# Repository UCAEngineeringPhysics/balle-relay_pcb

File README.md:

# balle-relay_pcb
PCB design for relaying balle's signals

## Schematic

## PCB0121

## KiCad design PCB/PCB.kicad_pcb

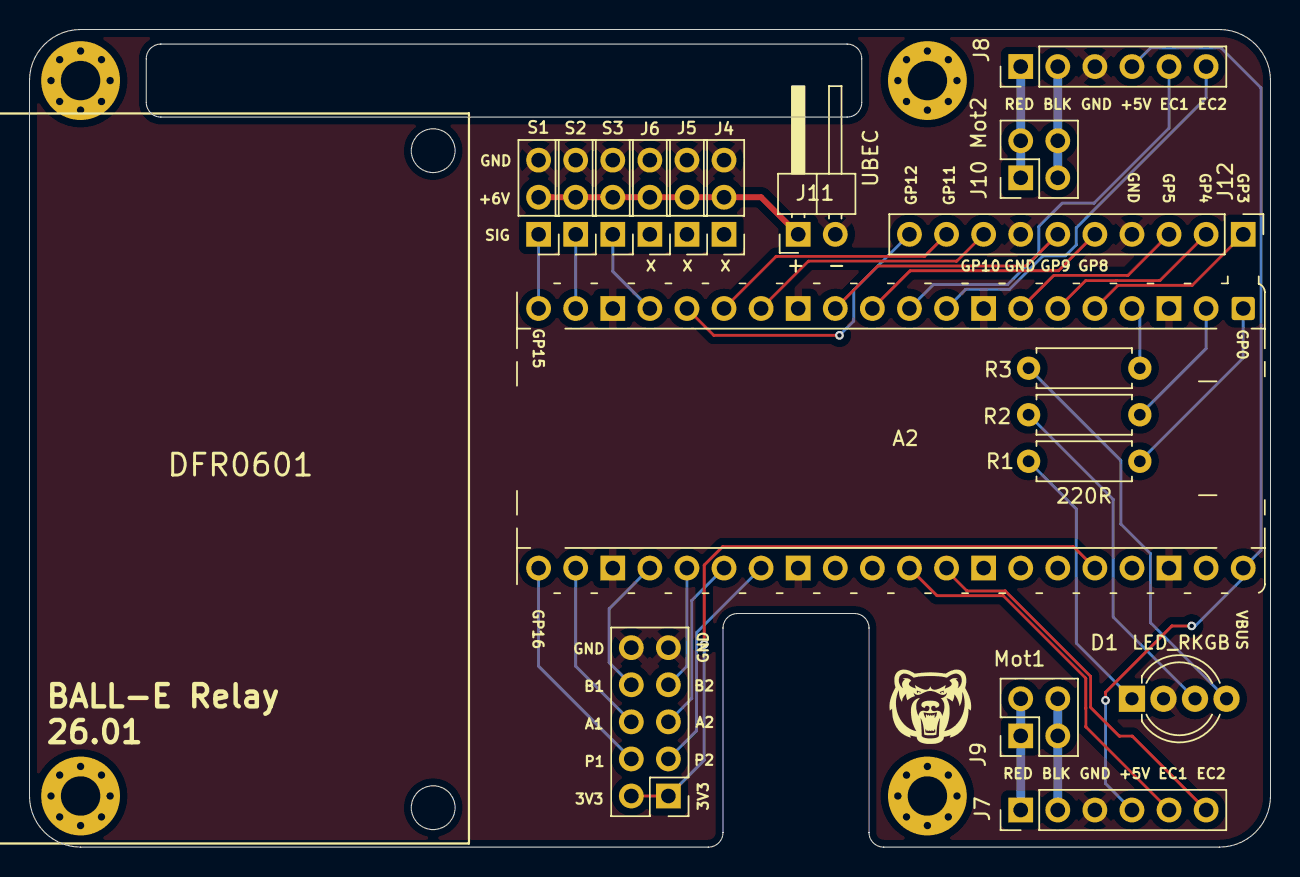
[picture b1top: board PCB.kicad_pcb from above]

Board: 4 copper layers, 85.0 x 56.0 mm, 22 parts (0 on the bottom side), 35 nets.

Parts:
A2: RaspberryPi_Pico; RaspberryPi_Pico_THT
D1: LED_RKGB; LED_D5.0mm-4_RGB_Wide_Pins
H1, H2, H3, H4: MountingHole_Pad; MountingHole_2.7mm_M2.5_Pad_Via
J4: Servo_Conn_4; PinHeader_1x03_P2.54mm_Vertical
J5: Servo_Conn_5; PinHeader_1x03_P2.54mm_Vertical
J6: Servo_Conn_6; PinHeader_1x03_P2.54mm_Vertical
J7: Mot1_Conn; PinHeader_1x06_P2.54mm_Vertical
J8: Mot2_Conn; PinHeader_1x06_P2.54mm_Vertical
J9: Mot1; PinHeader_2x02_P2.54mm_Vertical
J10: Mot2; PinHeader_2x02_P2.54mm_Vertical
J11: UBEC; PinHeader_1x02_P2.54mm_Horizontal
J12: Spare_GPIO_Conn; PinHeader_1x10_P2.54mm_Vertical
MOT_DRV_Conn1: Conn_02x05_Odd_Even; PinHeader_2x05_P2.54mm_Vertical
R1, R2, R3: 220R; R_Axial_DIN0207_L6.3mm_D2.5mm_P7.62mm_Horizontal
S1: Servo_Conn_1; PinHeader_1x03_P2.54mm_Vertical
S2: Servo_Conn_2; PinHeader_1x03_P2.54mm_Vertical
S3: Servo_Conn_3; PinHeader_1x03_P2.54mm_Vertical

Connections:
+3V3: A2.36 (3V3), MOT_DRV_Conn1.1, MOT_DRV_Conn1.2
+6V: J4.2, J5.2, J6.2, J11.1, S1.2, S2.2, S3.2
/BLK1: J7.2, J9.3, J9.4
/BLK2: J8.2, J10.3, J10.4
/BLUE: A2.4 (GPIO2), R3.2
/ENCA1: A2.31 (GPIO26_ADC0), J7.5
/ENCA2: A2.10 (GPIO7), J8.5
/ENCB1: A2.32 (GPIO27_ADC1), J7.6
/ENCB2: A2.9 (GPIO6), J8.6
/GPIO3: A2.5 (GPIO3), J12.1
/GPIO4: A2.6 (GPIO4), J12.2
/GPIO5: A2.7 (GPIO5), J12.3
/GPIO8: A2.11 (GPIO8), J12.5
/GPIO9: A2.12 (GPIO9), J12.6
/GPIO10: A2.14 (GPIO10), J12.8
/GPIO11: A2.15 (GPIO11), J12.9
/GPIO12: A2.16 (GPIO12), J12.10
/GREEN: A2.2 (GPIO1), R2.2
/INA1: A2.22 (GPIO17), MOT_DRV_Conn1.6
/INA2: A2.26 (GPIO20), MOT_DRV_Conn1.5
/INB1: A2.24 (GPIO18), MOT_DRV_Conn1.8
/INB2: A2.25 (GPIO19), MOT_DRV_Conn1.7
/PWM1: A2.21 (GPIO16), MOT_DRV_Conn1.4
/PWM2: A2.27 (GPIO21), MOT_DRV_Conn1.3
/RED: A2.1 (GPIO0), R1.2
/RED1: J7.1, J9.1, J9.2
/RED2: J8.1, J10.1, J10.2
/Srvo1_Sig: A2.20 (GPIO15), S1.1
/Srvo2_Sig: A2.19 (GPIO14), S2.1
/Srvo3_Sig: A2.17 (GPIO13), S3.1
GND: A2.3 (GND), A2.8 (GND), A2.13 (GND), A2.18 (GND), A2.23 (GND), A2.28 (GND), A2.33 (AGND), A2.38 (GND), D1.2 (K), J4.3, J5.3, J6.3, J7.3, J8.3, J11.2, J12.4, J12.7, MOT_DRV_Conn1.9, MOT_DRV_Conn1.10, S1.3, S2.3, S3.3
unnamed: D1.4 (BA), R3.1
unnamed: D1.3 (GA), R2.1
unnamed: D1.1 (RA), R1.1
VBUS: A2.40 (VBUS), J7.4, J8.4

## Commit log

2025-12-31 add Micha's design in 2025
2025-12-31 upload sch and pcb files
2025-12-31 update motor driver connection
2025-12-31 update sch with new motor driver connections and servos
2025-12-31 modify micha's notes
2025-12-31 update motor connections
2025-12-31 update peripheral connections
2026-01-05 update sch
2026-01-05 assign footprints
2026-01-05 update pcb
2026-01-21 update pico footprint
2026-01-21 set mounting holes
2026-01-22 update pcb layout
2026-01-22 pour copper to GND
2026-01-22 wire up
2026-01-22 update pcb0121 pic
2026-01-22 add schematic
2026-02-01 update PCB labeling and gerber
